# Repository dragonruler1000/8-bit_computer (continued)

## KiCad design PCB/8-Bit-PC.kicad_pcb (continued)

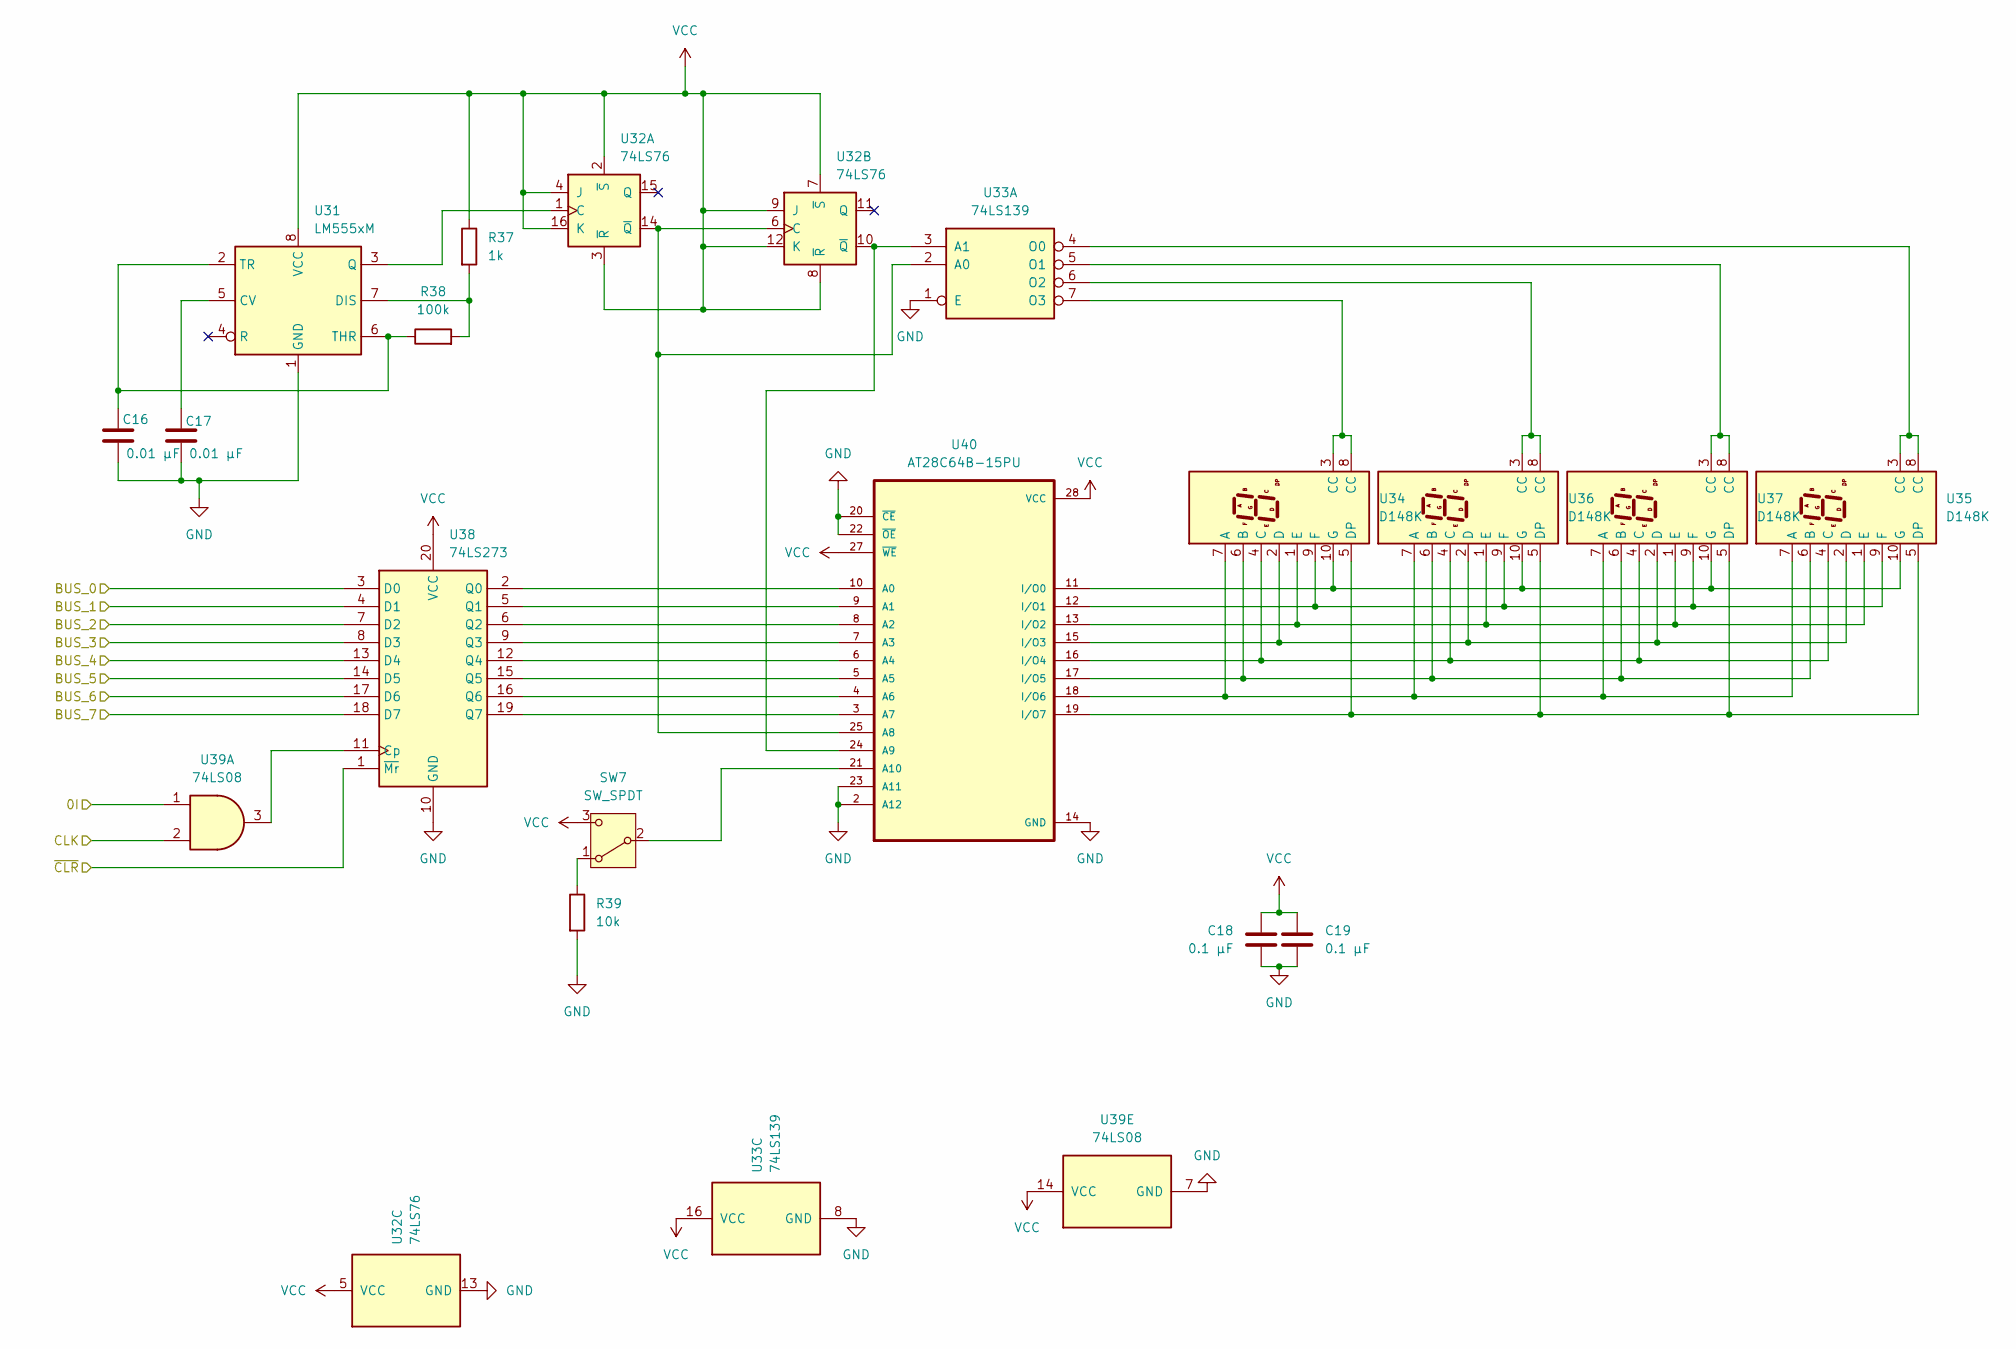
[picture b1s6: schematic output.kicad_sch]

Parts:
C16, C17: 0.01 µF; C_Radial_D5.0mm_H5.0mm_P2.00mm
C18, C19: 0.1 µF; C_Radial_D5.0mm_H5.0mm_P2.00mm
R37: 1k; R_Axial_DIN0207_L6.3mm_D2.5mm_P7.62mm_Horizontal
R38: 100k; R_Axial_DIN0207_L6.3mm_D2.5mm_P7.62mm_Horizontal
R39: 10k; R_Axial_DIN0207_L6.3mm_D2.5mm_P7.62mm_Horizontal
SW7: SW_SPDT; SW_SPDT_CK_JS102011SAQN
U31: LM555xM; SOIC-8_3.9x4.9mm_P1.27mm
U32: 74LS76; DIP-16_W7.62mm
U33: 74LS139; DIP-16_W7.62mm
U34, U35, U36, U37: D148K; D1X8K
U38: 74LS273; DIP254P762X508-20
U39: 74LS08; N14
U40: AT28C64B-15PU; DIP1555W45P254L3733H482Q28; PARTREV B

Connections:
BUS_0: U38.3 (D0); also elsewhere on the board
BUS_1: U38.4 (D1); also elsewhere on the board
BUS_2: U38.7 (D2); also elsewhere on the board
BUS_3: U38.8 (D3); also elsewhere on the board
BUS_4: U38.13 (D4); also elsewhere on the board
BUS_5: U38.14 (D5); also elsewhere on the board
BUS_6: U38.17 (D6); also elsewhere on the board
BUS_7: U38.18 (D7); also elsewhere on the board
CLK: U39.2; also elsewhere on the board
GND: C16.2, C17.2, C18.2, C19.2, R39.2, U31.1 (GND), U32.13 (GND), U33.1 (E), U33.8 (GND), U38.10 (GND), U39.7 (GND), U40.2 (A12), U40.14 (GND), U40.20 (~CE), U40.22 (~OE), U40.23 (A11); also elsewhere on the board
unnamed: R39.1, SW7.1 (A)
unnamed: SW7.2 (B), U40.21 (A10)
unnamed: C17.1, U31.5 (CV)
unnamed: R37.2, R38.2, U31.7 (DIS)
unnamed: U31.3 (Q), U32.1 (C)
unnamed: C16.1, R38.1, U31.2 (TR), U31.6 (THR)
unnamed: U32.6 (C), U32.14 (~Q), U33.2 (A0), U40.25 (A8)
unnamed: U32.10 (~Q), U33.3 (A1), U40.24 (A9)
unnamed: U33.4 (O0), U35.3 (CC), U35.8 (CC)
unnamed: U33.5 (O1), U37.3 (CC), U37.8 (CC)
unnamed: U33.6 (O2), U36.3 (CC), U36.8 (CC)
unnamed: U33.7 (O3), U34.3 (CC), U34.8 (CC)
unnamed: U34.7 (A), U35.7 (A), U36.7 (A), U37.7 (A), U40.18 (I/O6)
unnamed: U34.6 (B), U35.6 (B), U36.6 (B), U37.6 (B), U40.17 (I/O5)
unnamed: U34.4 (C), U35.4 (C), U36.4 (C), U37.4 (C), U40.16 (I/O4)
unnamed: U34.2 (D), U35.2 (D), U36.2 (D), U37.2 (D), U40.15 (I/O3)
unnamed: U34.5 (DP), U35.5 (DP), U36.5 (DP), U37.5 (DP), U40.19 (I/O7)
unnamed: U34.1 (E), U35.1 (E), U36.1 (E), U37.1 (E), U40.13 (I/O2)
unnamed: U34.9 (F), U35.9 (F), U36.9 (F), U37.9 (F), U40.12 (I/O1)
unnamed: U34.10 (G), U35.10 (G), U36.10 (G), U37.10 (G), U40.11 (I/O0)
unnamed: U38.11 (Cp), U39.3
unnamed: U38.2 (Q0), U40.10 (A0)
unnamed: U38.5 (Q1), U40.9 (A1)
unnamed: U38.6 (Q2), U40.8 (A2)
unnamed: U38.9 (Q3), U40.7 (A3)
unnamed: U38.12 (Q4), U40.6 (A4)
unnamed: U38.15 (Q5), U40.5 (A5)
unnamed: U38.16 (Q6), U40.4 (A6)
unnamed: U38.19 (Q7), U40.3 (A7)
OI: U39.1; also elsewhere on the board
VCC: C18.1, C19.1, R37.1, SW7.3 (C), U31.8 (VCC), U32.2 (~S), U32.3 (~R), U32.4 (J), U32.5 (VCC), U32.7 (~S), U32.8 (~R), U32.9 (J), U32.12 (K), U32.16 (K), U33.16 (VCC), U38.20 (VCC), U39.14 (VCC), U40.27 (~WE), U40.28 (VCC); also elsewhere on the board
~CLR: U38.1 (~Mr); also elsewhere on the board

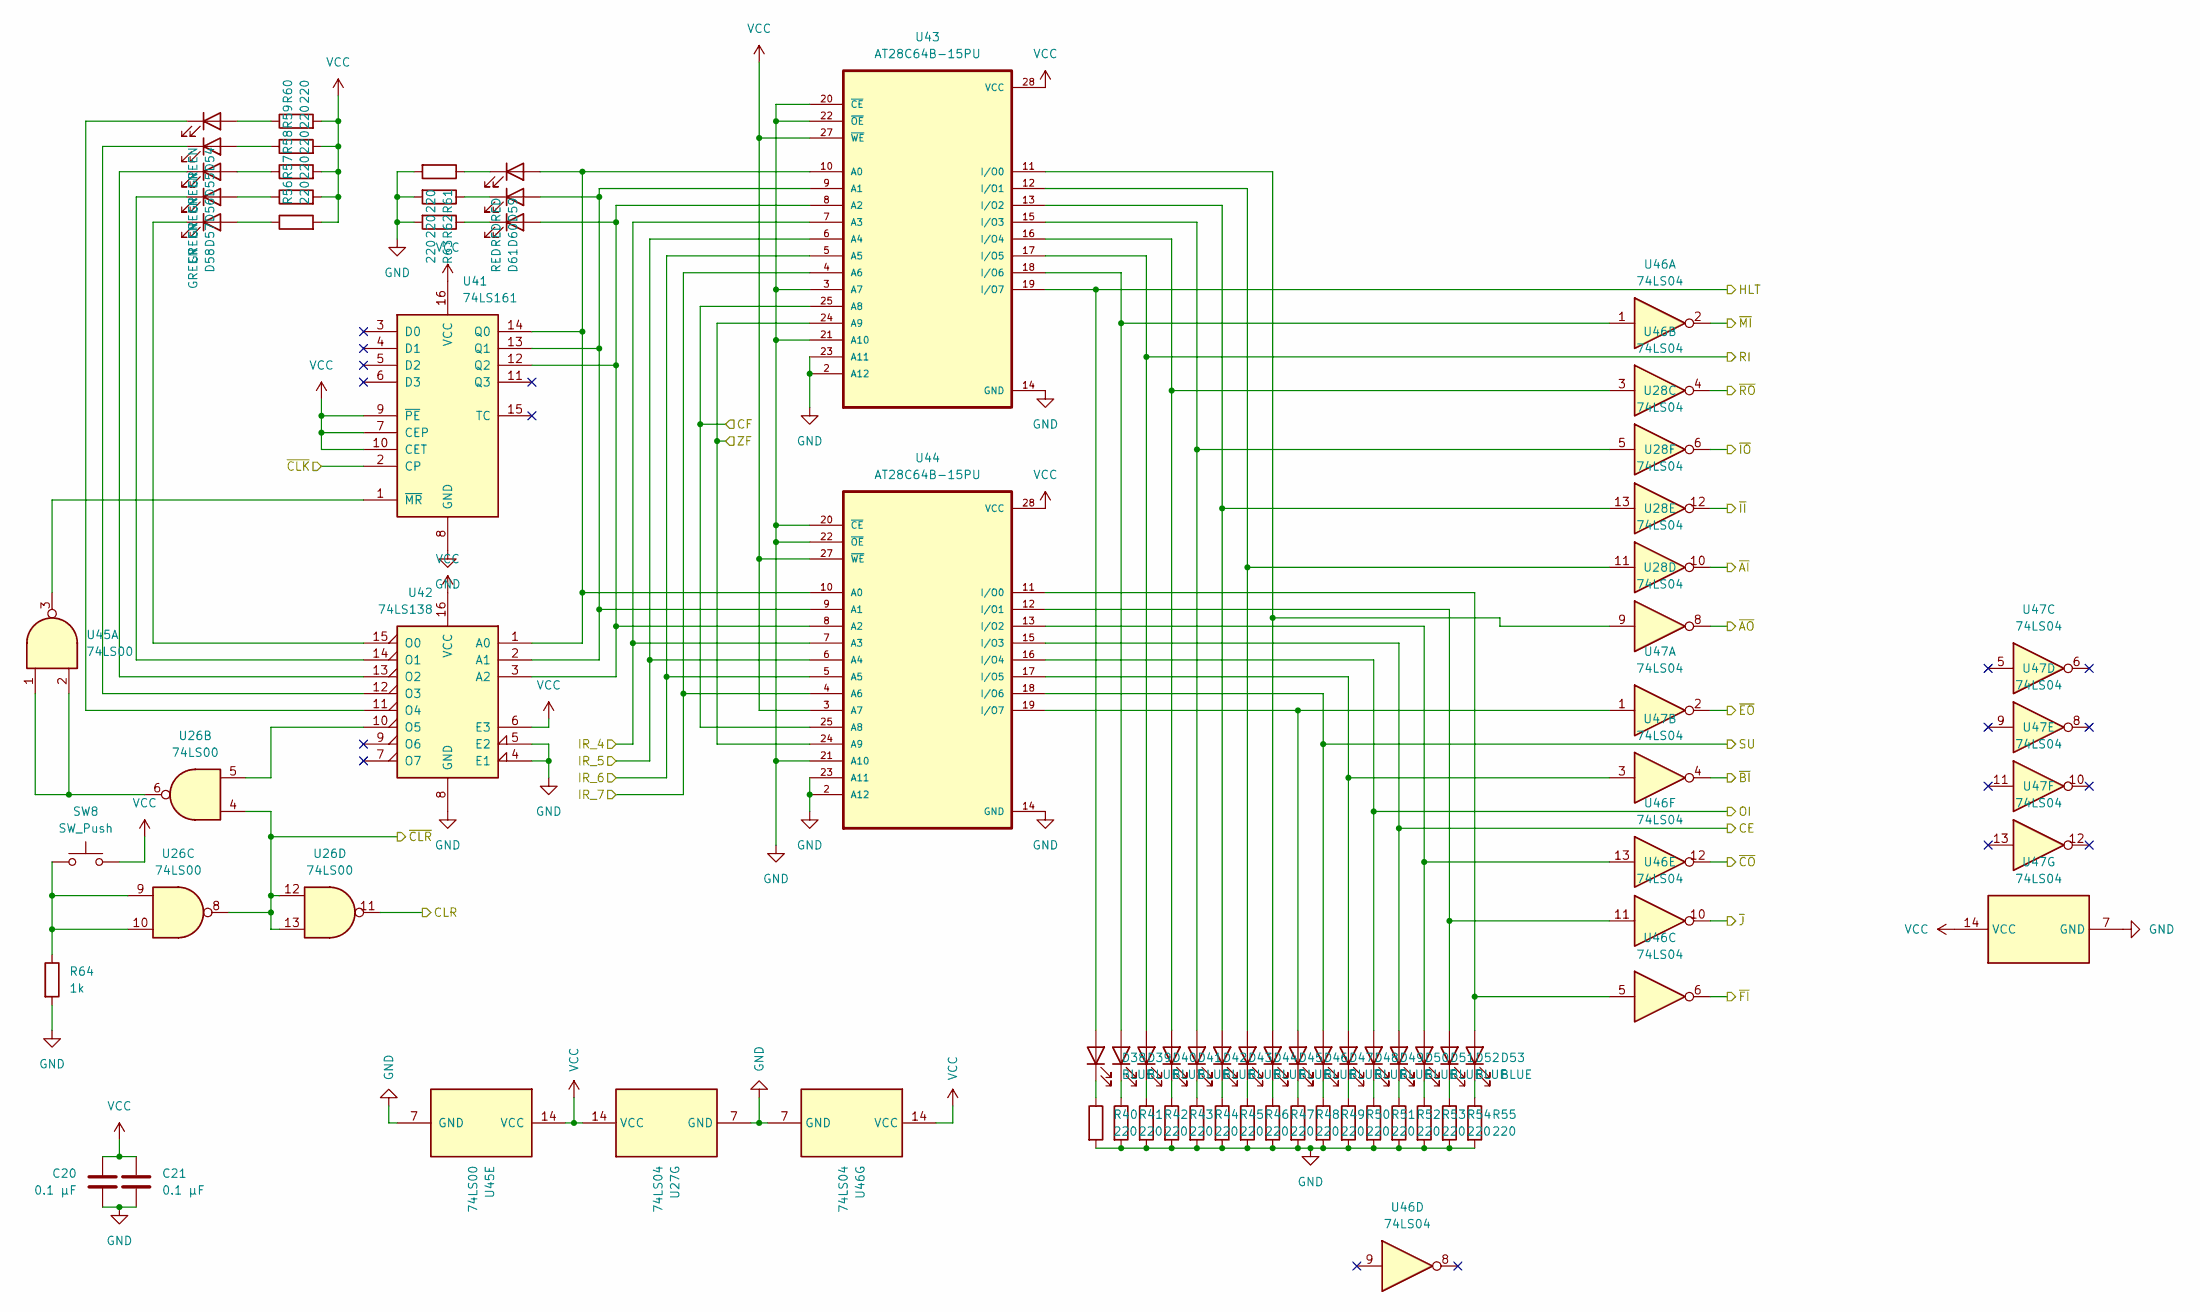
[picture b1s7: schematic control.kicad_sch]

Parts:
C20, C21: 0.1 µF; C_Radial_D5.0mm_H5.0mm_P2.00mm
D38, D39, D40, D41, D42, D43, D44, D45, D46, D47, D48, D49, D50, D51, D52, D53: BLUE; LED_D3.0mm
D54, D55, D56, D57, D58: GREEN; LED_D3.0mm
D59, D60, D61: RED; LED_D3.0mm
R40, R41, R42, R43, R44, R45, R46, R47, R48, R49, R50, R51, R52, R53, R54, R55, R56, R57, R58, R59, R60, R61, R62, R63: 220; R_Axial_DIN0207_L6.3mm_D2.5mm_P7.62mm_Horizontal
R64: 1k; R_Axial_DIN0207_L6.3mm_D2.5mm_P7.62mm_Horizontal
SW8: SW_Push; SW_PUSH_6mm
U26, U45: 74LS00; N14
U27, U28, U46, U47: 74LS04; N14
U41: 74LS161; N16
U42: 74LS138; N16
U43, U44: AT28C64B-15PU; DIP1555W45P254L3733H482Q28; PARTREV B

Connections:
CE: D50.2 (A), U44.15 (I/O3); also elsewhere on the board
CF: U43.25 (A8), U44.25 (A8); also elsewhere on the board
CLR: U26.11; also elsewhere on the board
GND: C20.2, C21.2, R40.2, R41.2, R42.2, R43.2, R44.2, R45.2, R46.2, R47.2, R48.2, R49.2, R50.2, R51.2, R52.2, R53.2, R54.2, R55.2, R61.2, R62.2, R63.2, R64.2, U27.7 (GND), U41.8 (GND), U42.4 (E1), U42.5 (E2), U42.8 (GND), U43.2 (A12), U43.3 (A7), U43.14 (GND), U43.20 (~CE), U43.21 (A10), U43.22 (~OE), U43.23 (A11), U44.2 (A12), U44.14 (GND), U44.20 (~CE), U44.21 (A10), U44.22 (~OE), U44.23 (A11), U45.7 (GND), U46.7 (GND), U47.7 (GND); also elsewhere on the board
HLT: D38.2 (A), U43.19 (I/O7); also elsewhere on the board
IR_4: U43.7 (A3), U44.7 (A3); also elsewhere on the board
IR_5: U43.6 (A4), U44.6 (A4); also elsewhere on the board
IR_6: U43.5 (A5), U44.5 (A5); also elsewhere on the board
IR_7: U43.4 (A6), U44.4 (A6); also elsewhere on the board
unnamed: D38.1 (K), R40.1
unnamed: D39.2 (A), U43.18 (I/O6), U46.1
unnamed: D39.1 (K), R41.1
unnamed: D40.1 (K), R42.1
unnamed: D41.2 (A), U43.16 (I/O4), U46.3
unnamed: D41.1 (K), R43.1
unnamed: D42.2 (A), U28.5, U43.15 (I/O3)
unnamed: D42.1 (K), R44.1
unnamed: D43.2 (A), U28.13, U43.13 (I/O2)
unnamed: D43.1 (K), R45.1
unnamed: D44.2 (A), U28.11, U43.12 (I/O1)
unnamed: D44.1 (K), R46.1
unnamed: D45.2 (A), U28.9, U43.11 (I/O0)
unnamed: D45.1 (K), R47.1
unnamed: D46.2 (A), U44.19 (I/O7), U47.1
unnamed: D46.1 (K), R48.1
unnamed: D47.1 (K), R49.1
unnamed: D48.2 (A), U44.17 (I/O5), U47.3
unnamed: D48.1 (K), R50.1
unnamed: D49.1 (K), R51.1
unnamed: D50.1 (K), R52.1
unnamed: D51.2 (A), U44.13 (I/O2), U46.13
unnamed: D51.1 (K), R53.1
unnamed: D52.2 (A), U44.12 (I/O1), U46.11
unnamed: D52.1 (K), R54.1
unnamed: D53.2 (A), U44.11 (I/O0), U46.5
unnamed: D53.1 (K), R55.1
unnamed: D54.2 (A), R60.1
unnamed: D54.1 (K), U42.11 (O4)
unnamed: D55.2 (A), R59.1
unnamed: D55.1 (K), U42.12 (O3)
unnamed: D56.2 (A), R58.1
unnamed: D56.1 (K), U42.13 (O2)
unnamed: D57.2 (A), R57.1
unnamed: D57.1 (K), U42.14 (O1)
unnamed: D58.2 (A), R56.1
unnamed: D58.1 (K), U42.15 (O0)
unnamed: D59.2 (A), U41.14 (Q0), U42.1 (A0), U43.10 (A0), U44.10 (A0)
unnamed: D59.1 (K), R61.1
unnamed: D60.2 (A), U41.13 (Q1), U42.2 (A1), U43.9 (A1), U44.9 (A1)
unnamed: D60.1 (K), R62.1
unnamed: D61.2 (A), U41.12 (Q2), U42.3 (A2), U43.8 (A2), U44.8 (A2)
unnamed: D61.1 (K), R63.1
unnamed: R64.1, SW8.1, U26.9, U26.10
unnamed: U26.6, U45.1, U45.2
unnamed: U41.1 (~MR), U45.3
unnamed: U26.5, U42.10 (O5)
OI: D49.2 (A), U44.16 (I/O4); also elsewhere on the board
RI: D40.2 (A), U43.17 (I/O5); also elsewhere on the board
SU: D47.2 (A), U44.18 (I/O6); also elsewhere on the board
VCC: C20.1, C21.1, R56.2, R57.2, R58.2, R59.2, R60.2, SW8.2, U27.14 (VCC), U41.7 (CEP), U41.9 (~PE), U41.10 (CET), U41.16 (VCC), U42.6 (E3), U42.16 (VCC), U43.27 (~WE), U43.28 (VCC), U44.3 (A7), U44.27 (~WE), U44.28 (VCC), U45.14 (VCC), U46.14 (VCC), U47.14 (VCC); also elsewhere on the board
ZF: U43.24 (A9), U44.24 (A9); also elsewhere on the board
~AI: U28.10; also elsewhere on the board
~AO: U28.8; also elsewhere on the board
~BI: U47.4; also elsewhere on the board
~CLK: U41.2 (CP); also elsewhere on the board
~CLR: U26.4, U26.8, U26.12, U26.13; also elsewhere on the board
~CO: U46.12; also elsewhere on the board
~EO: U47.2; also elsewhere on the board
~FI: U46.6; also elsewhere on the board
~II: U28.12; also elsewhere on the board
~IO: U28.6; also elsewhere on the board
~J: U46.10; also elsewhere on the board
~MI: U46.2; also elsewhere on the board
~RO: U46.4; also elsewhere on the board

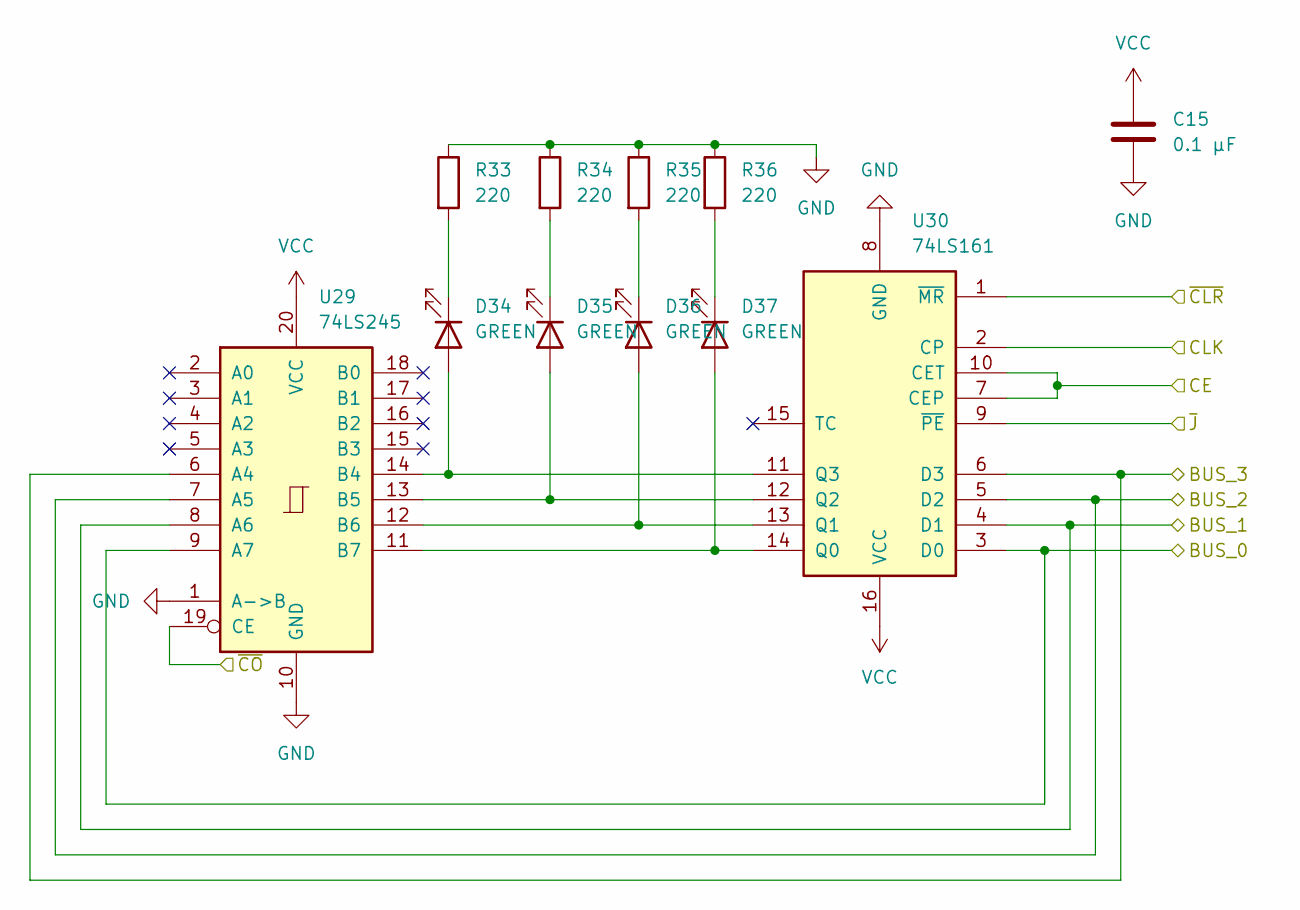
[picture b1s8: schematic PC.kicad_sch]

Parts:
C15: 0.1 µF; C_Radial_D5.0mm_H5.0mm_P2.00mm
D34, D35, D36, D37: GREEN; LED_D3.0mm
R33, R34, R35, R36: 220; R_Axial_DIN0207_L6.3mm_D2.5mm_P7.62mm_Horizontal
U29: 74LS245; DIP254P762X508-20
U30: 74LS161; N16

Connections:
BUS_0: U29.9 (A7), U30.3 (D0); also elsewhere on the board
BUS_1: U29.8 (A6), U30.4 (D1); also elsewhere on the board
BUS_2: U29.7 (A5), U30.5 (D2); also elsewhere on the board
BUS_3: U29.6 (A4), U30.6 (D3); also elsewhere on the board
CE: U30.7 (CEP), U30.10 (CET); also elsewhere on the board
CLK: U30.2 (CP); also elsewhere on the board
GND: C15.2, R33.1, R34.1, R35.1, R36.1, U29.1 (A->B), U29.10 (GND), U30.8 (GND); also elsewhere on the board
unnamed: D34.2 (A), U29.14 (B4), U30.11 (Q3)
unnamed: D34.1 (K), R33.2
unnamed: D35.2 (A), U29.13 (B5), U30.12 (Q2)
unnamed: D35.1 (K), R34.2
unnamed: D36.2 (A), U29.12 (B6), U30.13 (Q1)
unnamed: D36.1 (K), R35.2
unnamed: D37.2 (A), U29.11 (B7), U30.14 (Q0)
unnamed: D37.1 (K), R36.2
VCC: C15.1, U29.20 (VCC), U30.16 (VCC); also elsewhere on the board
~CLR: U30.1 (~MR); also elsewhere on the board
~CO: U29.19 (CE); also elsewhere on the board
~J: U30.9 (~PE); also elsewhere on the board

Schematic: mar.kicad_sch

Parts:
C11: 0.1 µF; C_Radial_D5.0mm_H5.0mm_P2.00mm
D20, D21, D22, D23: YELLOW; LED_D3.0mm
D24: RED; LED_D3.0mm
D25: GREEN; LED_D3.0mm
R18, R19: 1K; R_Axial_DIN0207_L6.3mm_D2.5mm_P7.62mm_Horizontal
R20, R21, R22, R23: 220; R_Axial_DIN0207_L6.3mm_D2.5mm_P7.62mm_Horizontal
SW3: SW_DIP_x04; SW_DIP_SPSTx04_Slide_6.7x11.72mm_W7.62mm_P2.54mm_LowProfile
SW4: SW_SPDT; SW_SPDT_CK_JS102011SAQN
U18: 74LS157; N16
U19: 74LS173; SN74LS173AN

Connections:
/MAR/A0: D23.2 (A), U18.12 (Zd); also elsewhere on the board
/MAR/A1: D22.2 (A), U18.9 (Zc); also elsewhere on the board
/MAR/A2: D21.2 (A), U18.7 (Zb); also elsewhere on the board
/MAR/A3: D20.2 (A), U18.4 (Za); also elsewhere on the board
/MAR/PROG: D24.1 (K), SW3.1, SW3.2, SW3.5, SW3.6, SW4.1 (A), U18.1 (S), U18.2 (I0a), U18.3 (I1a), U18.5 (I0b), U18.6 (I1b), U18.10 (I1c), U18.11 (I0c), U18.13 (I1d), U18.14 (I0d), U19.3 (Q0), U19.4 (Q1), U19.5 (Q2), U19.6 (Q3); also elsewhere on the board
BUS_0: U19.11 (D3); also elsewhere on the board
BUS_1: U19.12 (D2); also elsewhere on the board
BUS_2: U19.13 (D1); also elsewhere on the board
BUS_3: U19.14 (D0); also elsewhere on the board
CLK: U19.7 (Cp); also elsewhere on the board
CLR: U19.15 (Mr); also elsewhere on the board
GND: C11.2, R20.2, R21.2, R22.2, R23.2, SW3.3, SW3.4, SW3.7, SW3.8, SW4.2 (B), U18.8 (GND), U18.15 (E), U19.1 (Oe1), U19.2 (Oe2), U19.8 (GND); also elsewhere on the board
unnamed: D20.1 (K), R20.1
unnamed: D21.1 (K), R21.1
unnamed: D22.1 (K), R22.1
unnamed: D23.1 (K), R23.1
unnamed: D24.2 (A), R18.2
unnamed: D25.2 (A), R19.2
unnamed: D25.1 (K), SW4.3 (C)
VCC: C11.1, R18.1, R19.1, U18.16 (VCC), U19.16 (VCC); also elsewhere on the board
~MI: U19.9 (E1), U19.10 (E2); also elsewhere on the board

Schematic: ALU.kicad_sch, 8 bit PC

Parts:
C9, C10: 0.1 µF; C_Radial_D5.0mm_H5.0mm_P2.00mm
D10, D14: GREEN; LED_D3.0mm
D11, D12, D13, D15, D16, D17, D18, D19: RED; LED_D3.0mm
R8, R9, R10, R11, R12, R13, R14, R15, R16, R17: 220; R_Axial_DIN0207_L6.3mm_D2.5mm_P7.62mm_Horizontal
U10: 74LS08; DIP-14_W7.62mm
U11: 74LS02; N14
U12: 74LS173; DIP-16_W7.62mm
U13, U14: 74LS283; DIP-16_W7.62mm
U15: 74LS86; N14
U16: 74LS86; DIP-14_W7.62mm
U17: 74LS245; DIP254P762X508-20

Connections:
/ALU/A_0: U14.5 (A1); also elsewhere on the board
/ALU/A_1: U14.3 (A2); also elsewhere on the board
/ALU/A_2: U14.14 (A3); also elsewhere on the board
/ALU/A_3: U14.12 (A4); also elsewhere on the board
/ALU/A_4: U13.5 (A1); also elsewhere on the board
/ALU/A_5: U13.3 (A2); also elsewhere on the board
/ALU/A_6: U13.14 (A3); also elsewhere on the board
/ALU/A_7: U13.12 (A4); also elsewhere on the board
/ALU/B_0: U16.4; also elsewhere on the board
/ALU/B_1: U16.1; also elsewhere on the board
/ALU/B_2: U16.12; also elsewhere on the board
/ALU/B_3: U16.9; also elsewhere on the board
/ALU/B_4: U15.4; also elsewhere on the board
/ALU/B_5: U15.1; also elsewhere on the board
/ALU/B_6: U15.12; also elsewhere on the board
/ALU/B_7: U15.9; also elsewhere on the board
BUS_0: U17.11 (B7); also elsewhere on the board
BUS_1: U17.12 (B6); also elsewhere on the board
BUS_2: U17.13 (B5); also elsewhere on the board
BUS_3: U17.14 (B4); also elsewhere on the board
BUS_4: U17.15 (B3); also elsewhere on the board
BUS_5: U17.16 (B2); also elsewhere on the board
BUS_6: U17.17 (B1); also elsewhere on the board
BUS_7: U17.18 (B0); also elsewhere on the board
CF: D14.2 (A), U12.3 (Q0); also elsewhere on the board
CLK: U12.7 (Cp); also elsewhere on the board
CLR: U12.15 (Mr); also elsewhere on the board
GND: C9.2, C10.2, R8.2, R9.2, R10.1, R11.2, R12.2, R13.2, R14.2, R15.2, R16.1, R17.2, U10.7 (GND), U11.7 (GND), U12.1 (Oe1), U12.2 (Oe2), U12.8 (GND), U13.8 (GND), U14.8 (GND), U15.7 (GND), U16.7 (GND), U17.10 (GND); also elsewhere on the board
unnamed: D10.1 (K), R10.2
unnamed: D11.2 (A), U11.2, U13.10 (S4), U17.2 (A0)
unnamed: D11.1 (K), R9.1
unnamed: D12.2 (A), U11.3, U13.13 (S3), U17.3 (A1)
unnamed: D12.1 (K), R11.1
unnamed: D13.2 (A), U11.5, U13.1 (S2), U17.4 (A2)
unnamed: D13.1 (K), R12.1
unnamed: D14.1 (K), R8.1
unnamed: D15.2 (A), U11.6, U13.4 (S1), U17.5 (A3)
unnamed: D15.1 (K), R13.1
unnamed: D16.2 (A), U11.8, U14.10 (S4), U17.6 (A4)
unnamed: D16.1 (K), R14.1
unnamed: D17.2 (A), U11.9, U14.13 (S3), U17.7 (A5)
unnamed: D17.1 (K), R15.1
unnamed: D18.2 (A), U11.11, U14.1 (S2), U17.8 (A6)
unnamed: D18.1 (K), R16.2
unnamed: D19.2 (A), U11.12, U14.4 (S1), U17.9 (A7)
unnamed: D19.1 (K), R17.1
unnamed: U10.1, U11.4
unnamed: U10.2, U11.1
unnamed: U10.3, U10.5
unnamed: U10.4, U10.8
unnamed: U10.9, U11.13
unnamed: U10.10, U11.10
unnamed: U12.14 (D0), U13.9 (C4)
unnamed: U10.6, U12.13 (D1)
unnamed: U13.6 (B1), U15.6
unnamed: U13.2 (B2), U15.3
unnamed: U13.15 (B3), U15.11
unnamed: U13.11 (B4), U15.8
unnamed: U13.7 (C0), U14.9 (C4)
unnamed: U14.6 (B1), U16.6
unnamed: U14.2 (B2), U16.11
unnamed: U14.15 (B3), U16.3
unnamed: U14.11 (B4), U16.8
SU: U14.7 (C0), U15.2, U15.5, U15.10, U15.13, U16.2, U16.5, U16.10, U16.13; also elsewhere on the board
VCC: C9.1, C10.1, U10.14 (VCC), U11.14 (VCC), U12.16 (VCC), U13.16 (VCC), U14.16 (VCC), U15.14 (VCC), U16.14 (VCC), U17.1 (A->B), U17.20 (VCC); also elsewhere on the board
ZF: D10.2 (A), U12.4 (Q1); also elsewhere on the board
~EO: U17.19 (CE); also elsewhere on the board
~FI: U12.9 (E1), U12.10 (E2); also elsewhere on the board

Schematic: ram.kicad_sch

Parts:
C12, C13: 0.1 µF; C_Radial_D5.0mm_H5.0mm_P2.00mm
C14: 0.01 µF; C_Radial_D5.0mm_H5.0mm_P2.00mm
D26, D27, D28, D29, D30, D31, D32, D33: RED; LED_D3.0mm
R24, R25, R26, R27, R28, R29, R30, R31: 220; R_Axial_DIN0207_L6.3mm_D2.5mm_P7.62mm_Horizontal
R32: 1K; R_Axial_DIN0207_L6.3mm_D2.5mm_P7.62mm_Horizontal
SW5: SW_DIP_x08; SW_DIP_SPSTx08_Slide_6.7x21.88mm_W7.62mm_P2.54mm_LowProfile
SW6: SW_Push; SW_PUSH_6mm
U5, U20, U22: 74LS04; DIP-14_W7.62mm
U21, U23: 74F189SC; SOIC16_9P9X3P9_ONS
U24, U51, U52: 74LS158; DIP-16_W7.62mm
U25: 74LS245; DIP254P762X508-20
U26: 74LS00; N14
U27, U28: 74LS04; N14

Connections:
/MAR/A0: U21.1 (A0), U23.1 (A0); also elsewhere on the board
/MAR/A1: U21.15 (A1), U23.15 (A1); also elsewhere on the board
/MAR/A2: U21.14 (A2), U23.14 (A2); also elsewhere on the board
/MAR/A3: U21.13 (A3), U23.13 (A3); also elsewhere on the board
/MAR/PROG: U24.1 (S), U51.1 (S), U52.1 (S); also elsewhere on the board
BUS_0: U24.10 (I1d), U25.11 (B7); also elsewhere on the board
BUS_1: U24.13 (I1c), U25.12 (B6); also elsewhere on the board
BUS_2: U24.6 (I1b), U25.13 (B5); also elsewhere on the board
BUS_3: U24.3 (I1a), U25.14 (B4); also elsewhere on the board
BUS_4: U25.15 (B3), U52.10 (I1d); also elsewhere on the board
BUS_5: U25.16 (B2), U52.13 (I1c); also elsewhere on the board
BUS_6: U25.17 (B1), U52.6 (I1b); also elsewhere on the board
BUS_7: U25.18 (B0), U52.3 (I1a); also elsewhere on the board
CLK: C14.1; also elsewhere on the board
GND: C12.2, C13.2, R24.2, R25.2, R26.2, R27.2, R28.2, R29.2, R30.2, R31.2, R32.2, SW5.3, SW5.4, SW5.7, SW5.8, SW5.11, SW5.12, SW5.15, SW5.16, SW6.1, U20.7 (GND), U21.2 (*CS), U21.8 (GND), U22.7 (GND), U23.2 (*CS), U23.8 (GND), U24.8 (GND), U24.15 (E), U25.10 (GND), U26.7 (GND), U28.7 (GND), U51.8 (GND), U51.15 (E), U52.8 (GND), U52.15 (E); also elsewhere on the board
unnamed: C14.2, R32.1, U26.1
unnamed: D26.2 (A), U25.2 (A0), U27.2
unnamed: D26.1 (K), R24.1
unnamed: D27.2 (A), U25.3 (A1), U27.4
unnamed: D27.1 (K), R25.1
unnamed: D28.2 (A), U25.4 (A2), U27.6
unnamed: D28.1 (K), R26.1
unnamed: D29.2 (A), U25.5 (A3), U27.8
unnamed: D29.1 (K), R27.1
unnamed: D30.2 (A), U25.6 (A4), U27.10
unnamed: D30.1 (K), R28.1
unnamed: D31.2 (A), U25.7 (A5), U27.12
unnamed: D31.1 (K), R29.1
unnamed: D32.2 (A), U25.8 (A6), U28.2
unnamed: D32.1 (K), R30.1
unnamed: D33.2 (A), U25.9 (A7), U28.4
unnamed: D33.1 (K), R31.1
unnamed: U21.5 (*O0), U27.1
unnamed: U21.7 (*O1), U27.3
unnamed: U21.9 (*O2), U27.5
unnamed: U21.11 (*O3), U27.9
unnamed: U20.2, U21.3 (*WE), U23.3 (*WE)
unnamed: U21.4 (D0), U22.2
unnamed: U5.4, U21.6 (D1)
unnamed: U5.6, U21.10 (D2)
unnamed: U20.8, U21.12 (D3)
unnamed: U23.5 (*O0), U28.3
unnamed: U23.7 (*O1), U28.1
unnamed: U23.9 (*O2), U27.13
unnamed: U23.11 (*O3), U27.11
unnamed: U20.12, U23.4 (D0)
unnamed: U5.10, U23.6 (D1)
unnamed: U20.6, U23.10 (D2)
unnamed: U20.4, U23.12 (D3)
unnamed: SW5.13, U24.2 (I0a)
unnamed: SW5.14, U24.5 (I0b)
unnamed: SW5.2, U24.14 (I0c)
unnamed: SW5.1, U24.11 (I0d)
unnamed: U20.5, U24.4 (Za)
unnamed: U20.3, U24.7 (Zb)
unnamed: U5.11, U24.12 (Zc)
unnamed: U20.13, U24.9 (Zd)
unnamed: SW6.2, U51.14 (I0c)
unnamed: U26.3, U51.13 (I1c)
unnamed: U20.1, U51.12 (Zc)
unnamed: SW5.9, U52.2 (I0a)
unnamed: SW5.10, U52.5 (I0b)
unnamed: SW5.6, U52.14 (I0c)
unnamed: SW5.5, U52.11 (I0d)
unnamed: U22.1, U52.4 (Za)
unnamed: U5.3, U52.7 (Zb)
unnamed: U5.5, U52.12 (Zc)
unnamed: U20.9, U52.9 (Zd)
RI: U26.2; also elsewhere on the board
VCC: C12.1, C13.1, U20.14 (VCC), U21.16 (VCC), U22.14 (VCC), U23.16 (VCC), U24.16 (VCC), U25.1 (A->B), U25.20 (VCC), U26.14 (VCC), U28.14 (VCC), U51.16 (VCC), U52.16 (VCC); also elsewhere on the board
~RO: U25.19 (CE); also elsewhere on the board

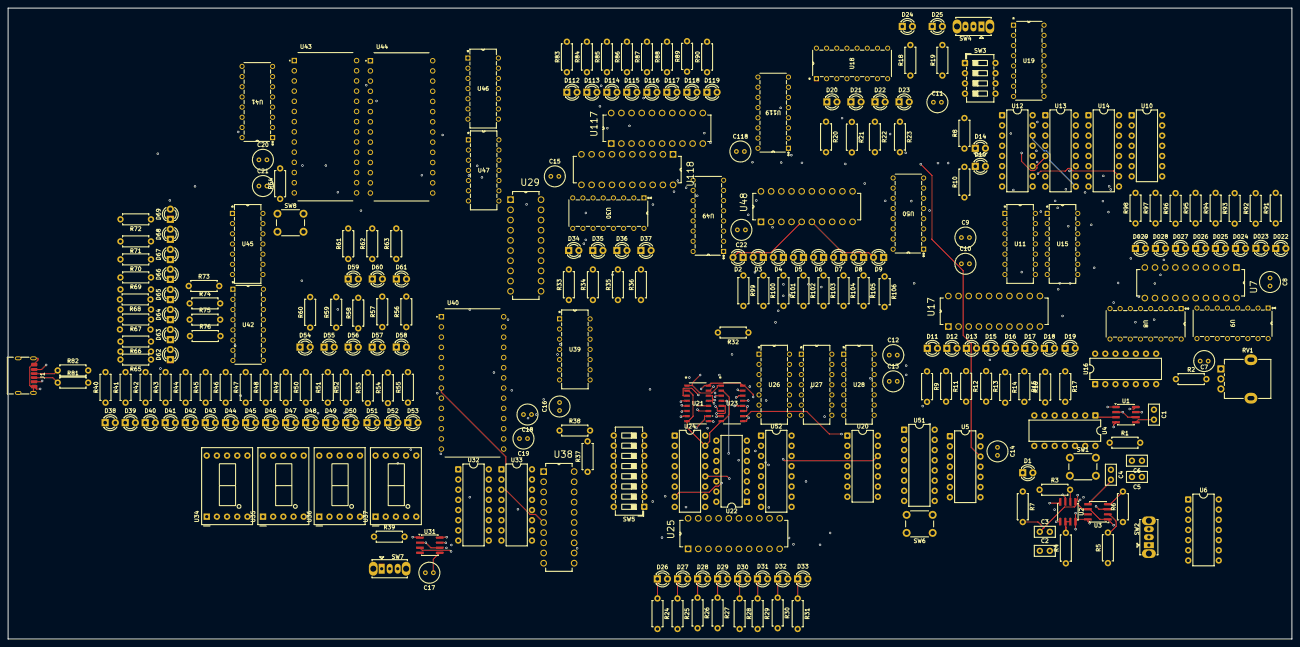
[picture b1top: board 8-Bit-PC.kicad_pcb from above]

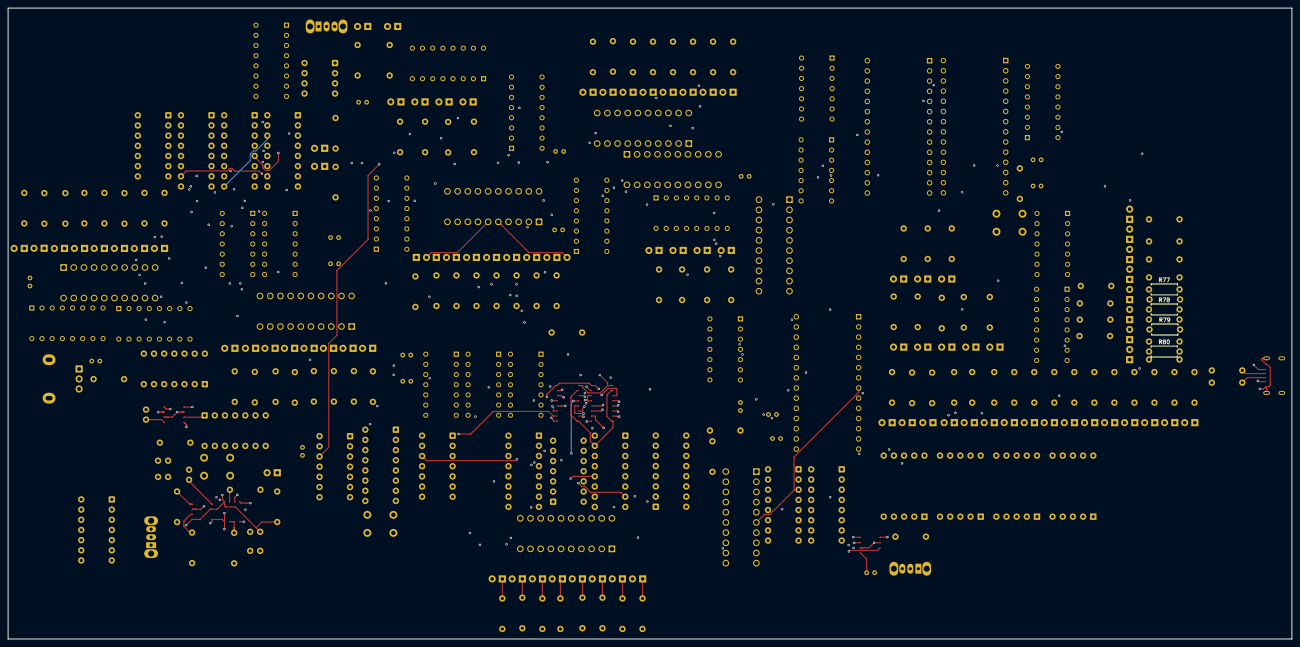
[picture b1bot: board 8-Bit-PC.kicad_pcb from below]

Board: 6 copper layers, 320.5 x 157.5 mm, 279 parts (4 on the bottom side), 293 nets.

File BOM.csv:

Reference,Qty,Value,DNP,Exclude from BOM,Exclude from Board,Footprint,Datasheet,MANUFACTURER,#
"C1,C2,C3,C4,C5,C6",6,0.01 µF,,,,Capacitor_THT:C_Disc_D5.0mm_W2.5mm_P2.50mm,~,,1
C7,1,1 µF,,,,Capacitor_THT:C_Radial_D5.0mm_H5.0mm_P2.00mm,,,2
"C8,C9,C10,C11,C12,C13,C15,C18,C19,C20,C21,C?",12,0.1 µF,,,,,~,,3
"C14,C16,C17",3,0.01 µF,,,,,~,,4
D1,1,BLUE,,,,LED_THT:LED_D3.0mm,~,,5
"D2,D3,D4,D5,D6,D7,D8,D9",8,RED,,,,LED_THT:LED_D3.0mm,~,,6
"D10,D20,D21,D22,D23,D26,D27,D28,D29,D30,D31,D32,D33,D37",14,LED,,,,,~,,7
"D11,D12,D13,D14,D15,D16,D17,D18,D19",9,LED,,,,LED_THT:LED_D1.8mm_W1.8mm_H2.4mm_Horizontal_O1.27mm_Z1.6mm,~,,8
"D24,D59,D60,D61,D62,D63,D64,D65,D66,D67,D68,D69",12,RED,,,,,~,,9
"D25,D34,D35,D36,D54,D55,D56,D57,D58",9,GREEN,,,,,~,,10
"D38,D39,D40,D41,D42,D43,D44,D45,D46,D47,D48,D49,D50,D51,D52,D53",16,BLUE,,,,,~,,11
"R1,R2,R3",3,1K,,,,Resistor_THT:R_Axial_DIN0207_L6.3mm_D2.5mm_P7.62mm_Horizontal,~,,12
"R4,R5,R6",3,R,,,,Resistor_THT:R_Axial_DIN0207_L6.3mm_D2.5mm_P7.62mm_Horizontal,~,,13
R7,1,220,,,,Resistor_THT:R_Axial_DIN0207_L6.3mm_D2.5mm_P7.62mm_Horizontal,~,,14
"R8,R9,R10,R11,R12,R13,R14,R15,R16,R17,R20,R21,R22,R23,R24,R25,R26,R27,R28,R29,R30,R31,R33,R34,R35,R36,R40,R41,R42,R43,R44,R45,R46,R47,R48,R49,R50,R51,R52,R53,R54,R55,R56,R57,R58,R59,R60,R61,R62,R63,R65,R66,R67,R68,R69,R70,R71,R72",58,220,,,,,~,,15
"R18,R19,R32",3,1K,,,,,~,,16
"R37,R64",2,1k,,,,,~,,17
R38,1,100k,,,,,~,,18
"R39,R73,R74,R75,R76,R77,R78,R79,R80",9,10k,,,,,~,,19
RV1,1,1M,,,,Potentiometer_THT:Potentiometer_Alpha_RD901F-40-00D_Single_Vertical,~,,20
"SW1,SW6,SW8",3,SW_Push,,,,,~,,21
"SW2,SW4,SW7",3,SW_SPDT,,,,,~,,22
SW3,1,SW_DIP_x04,,,,,~,,23
SW5,1,SW_DIP_x08,,,,,~,,24
"U1,U2,U3,U31",4,LM555xM,,,,Package_SO:SOIC-8_3.9x4.9mm_P1.27mm,http://www.ti.com/lit/ds/symlink/lm555.pdf,,25
"U4,U10",2,74LS08,,,,Package_DIP:DIP-14_W7.62mm,http://www.ti.com/lit/gpn/sn74LS08,,26
U5,1,74LS04,,,,Package_DIP:DIP-14_W7.62mm,http://www.ti.com/lit/gpn/sn74LS04,,27
U6,1,74LS32,,,,,http://www.ti.com/lit/gpn/sn74LS32,,28
"U7,U17,U25,U29,U?",5,74LS245,,,,,http://www.ti.com/lit/gpn/sn74LS245,,29
"U8,U9,U19,U?,U?",5,74LS173,,,,,http://www.ti.com/lit/gpn/sn74LS173,,30
U11,1,74LS02,,,,,http://www.ti.com/lit/gpn/sn74ls02,,31
U12,1,74LS173,,,,Package_DIP:DIP-16_W7.62mm,http://www.ti.com/lit/gpn/sn74LS173,,32
"U13,U14",2,74LS283,,,,Package_DIP:DIP-16_W7.62mm,http://www.ti.com/lit/gpn/sn74LS283,,33
"U15,U16",2,74LS86,,,,,74xx/74ls86.pdf,,34
"U18,U20,U22,U24",4,74LS157,,,,,http://www.ti.com/lit/gpn/sn74LS157,,35
"U21,U23",2,74189,,,,,https://eater.net/datasheets/74189.pdf,,36
"U26,U45",2,74LS00,,,,,http://www.ti.com/lit/gpn/sn74ls00,,37
"U27,U28,U46,U47",4,74LS04,,,,,http://www.ti.com/lit/gpn/sn74LS04,,38
"U30,U41",2,74LS161,,,,,http://www.ti.com/lit/gpn/sn74LS161,,39
U32,1,74LS76,,,,,http://www.ti.com/lit/gpn/sn74LS76,,40
U33,1,74LS139,,,,Package_DIP:DIP-16_W7.62mm,http://www.ti.com/lit/ds/symlink/sn74ls139a.pdf,,41
"U34,U35,U36,U37",4,D148K,,,,Display_7Segment:D1X8K,https://ia800903.us.archive.org/24/items/CTKD1x8K/Cromatek%2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,,42
U38,1,74LS273,,,,,http://www.ti.com/lit/gpn/sn74LS273,,43
U39,1,74LS08,,,,,http://www.ti.com/lit/gpn/sn74LS08,,44
"U40,U43,U44",3,AT28C64B-15PU,,,,AT28C64B_15PU:DIP1555W45P254L3733H482Q28,https://ww1.microchip.com/downloads/en/DeviceDoc/doc0270.pdf,Microchip Technology,45
U42,1,74LS138,,,,,http://www.ti.com/lit/gpn/sn74LS138,,46
,,,,,,,,,
,,,,,,,,,
,,,,,,,,,
,,,,,,,,,
,,,,,,,,,
,,,,,,,,,
,,,,,,,,,
,,,,,,,,,
,,,,,,,,,
,,,,,,,,,
,,,,,,,,,
,,,,,,,,,
,,,,,,,,,
,,,,,,,,,
![Screenshot_20251026_165409](/user-attachments/blobs/proxy/eyJfcmFpbHMiOnsiZGF0YSI6NTgyMCwicHVyIjoiYmxvYl9pZCJ9fQ==--4bd96d94e1b8c2c169f6b67b09845199ded7aaa9/Screenshot_20251026_165409.png),,,,,,,,,

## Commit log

2025-10-14 set up the clock module and started work on the a-register
2025-10-14 Made the a-register and edited it to make it work for the b-register
2025-10-19 Added the ALU and flags register schematic.
2025-10-22 set up the MAR module and got started on the RAM module
2025-10-26 Made the ram module as well as set up a custom symbol for the 74f189sj chip.
2025-10-26 Added the program counter
2025-10-26 moved the pcb stuff to the PCB folder to make organazizon in the future easier.
2025-10-26 got ready to add the cpu control and and out put modules
2025-10-28 Cleaned up the schematic and got started on assigning all the footprints to the symbols
2025-11-04 added more models to work with on my pcb
2025-11-04 got the PCB layed out into one group and started routing the traces and fixing DRC errors.
2025-11-05 Fixed a bunch of ERC errors so know there is only one remaining.
2025-11-06 Routed the traces for the ground
2025-11-06 routed the traces for the ground plane.
2025-11-07 finnished routing the PCB.
2025-11-08 rerouted my pvb to work with THT RAM and made my full BOM
2025-11-08 regenerate gerbers and remove stl file
2025-11-08 remove stl file
2025-11-08 added shipping cost to BOM
2025-11-08 moved the latest BOM from the PCB folder to the main folder
2025-11-08 fixed typos in BOM
2025-11-08 Update README with project details and images
    Added description and images for the 8-bit computer project.
2025-11-08 Added the microcode for the Computer
2025-11-08 Added a 3d model of the PBC
2025-11-08 Add BOM section to README
    Added a Bill of Materials (BOM) section with details on components, quantities, prices, and links for purchasing.
2025-11-08 Added wrl file for PCB.
2025-11-08 added a #d model of the case and pcb.
2025-11-08 Update README with usage instructions and images
    Added usage instructions and a 3D model image.
2025-11-08 Fix header formatting in README.md
    Corrected the header formatting for usage instructions.
2025-11-08 Revise usage instructions in README.md
    Updated usage instructions to indicate future additions.
2025-11-09 update BOM to use parts from LCSC
2025-11-09 removed stencil from BOM as i wont need it
2025-11-09 Revise BOM table with updated values and corrections
    Updated BOM table with new values and links, corrected typos, and added notes for clarity.
2025-11-09 Restore BOM.csv with updated items and prices
    Restored BOM.csv with updated quantities and prices.
2025-11-09 Remove stencil entry from README
    Removed stencil entry from the components list.
2025-11-09 Update BOM table and add shipping cost
2025-11-10 Add 3D model and PCB images to README
    Added images of the 3D model and PCB to the README.
2025-11-10 Fix formatting and update BOM section in README
2025-11-11 Add additional images to README.md
2025-11-11 Improve formatting in README.md
    Updated the README to include HTML line breaks for better formatting.
2025-11-11 Revise BOM with updated component details and costs
    Updated BOM table with new quantities, values, and links for components. Added shipping cost and adjusted running totals.
2025-11-11 updated BOM to include shipping and terrifs
2025-11-12 Update BOM to use cheaper componits for the capaciters
2025-11-12 add git ignore
2025-11-12 start rerouting the PCB to match the schematic changes
2025-11-12 rerouted the PCB to work with the latest version of the schematic
2025-11-18 Add decupling caps and reroute pcb. Updated BOM to match new number of caps
2025-11-18 updated BOM to match full prices
2025-11-18 Update BOM with customer numbers and pricing adjustments
    Added a customer number column to the BOM table and updated quantities and prices for several components.
2025-11-19 update pdf version of schematic
2025-11-21 Redoing PCB layout and fixed some signal flow convention errors
2025-11-27 update BOM to reflect cheaper prices and more acurate item ammounts, also worked on laying out the PCB.
2025-11-30 backing up before routing for easily going back if i mess up
2025-12-01 Backup just incase i mess up so i dont have to spend another 8 hours redoing the work up to this point.
2025-12-02 continued working on routing the pcb
2025-12-04 Finnised routing the pcb
2025-12-04 adding the plots for the pcb
2025-12-05 made sure the BOM was the latest version
2025-12-06 updated images in sanity check folder
2025-12-09 i really don't know
2025-12-09 update the BOM to reflect new prices
2025-12-09 Revise BOM quantities and prices
    Updated quantities and prices for various components in the BOM table.
2025-12-09 up date price for PCB
2025-12-09 Modify PCB and shipping cost details in README
    Updated PCB cost and shipping cost entries in the table.
2025-12-11 updated case to fit the new pcb
2025-12-11 Update README with new images and BOM
    Added additional images and BOM details to README.
2025-12-11 Update README with case description
    Added description about the case being split into two parts.
2025-12-11 Revise BOM with updated pricing and links
    Updated component prices, quantities, and links in the BOM section.
2025-12-11 update prices on BOM
2025-12-12 Update README with schematic and case details
    Added schematic images and updated case description.
2025-12-12 adding svgs of the pcb schematic
2025-12-12 update bom and add shopping cart images
2025-12-12 Adjust shipping cost and tariffs in README
    Updated shipping cost and tariffs to reflect new values.
